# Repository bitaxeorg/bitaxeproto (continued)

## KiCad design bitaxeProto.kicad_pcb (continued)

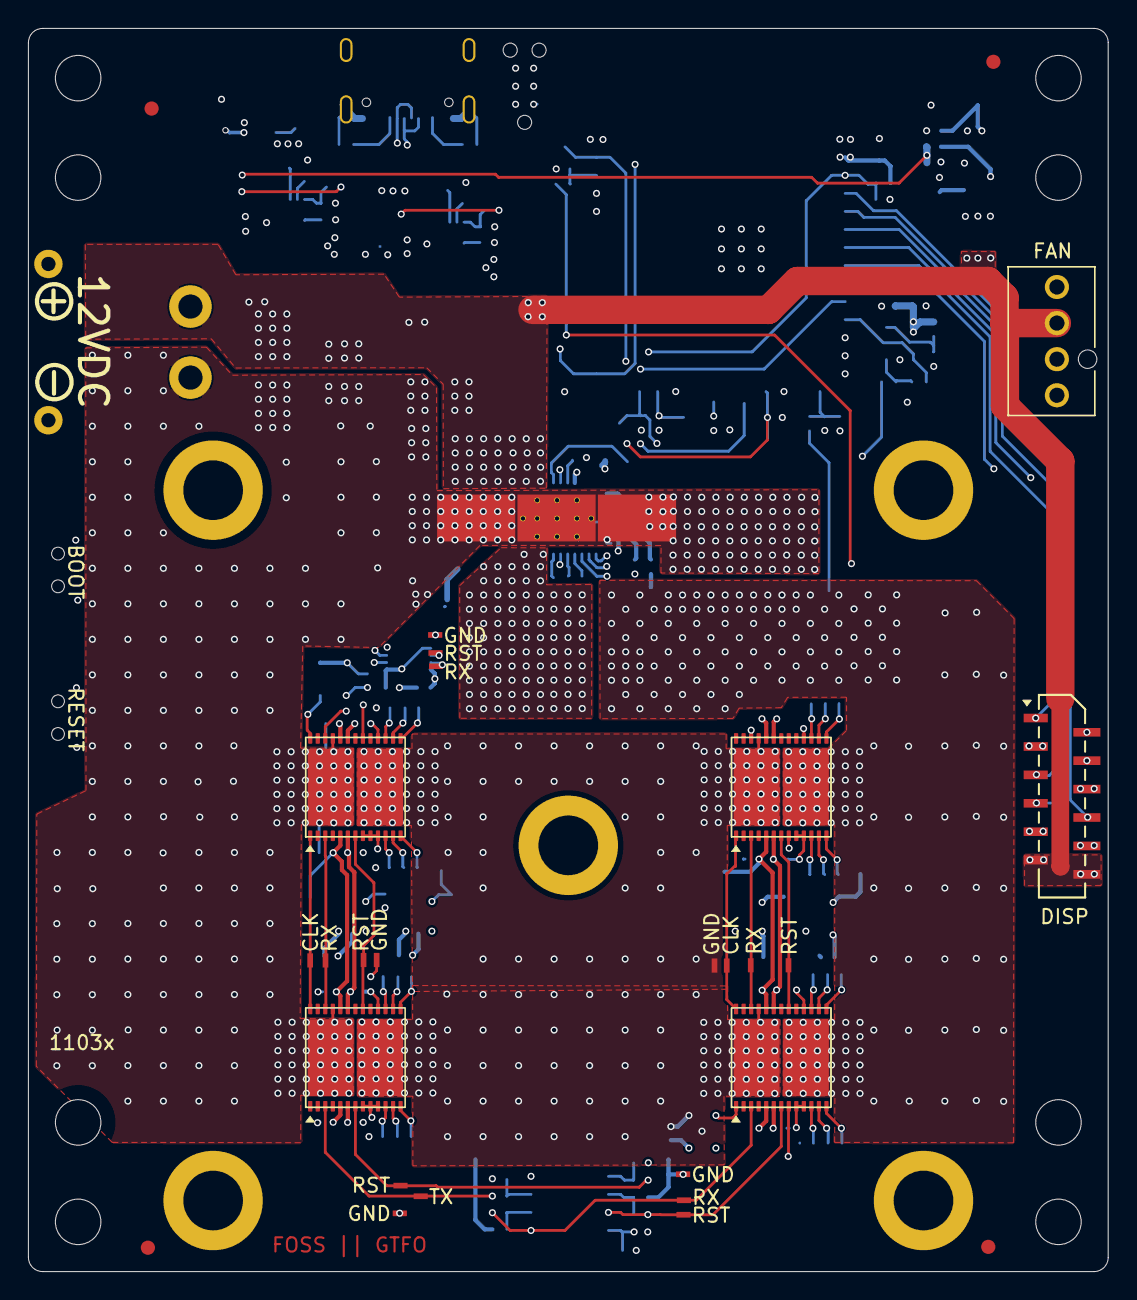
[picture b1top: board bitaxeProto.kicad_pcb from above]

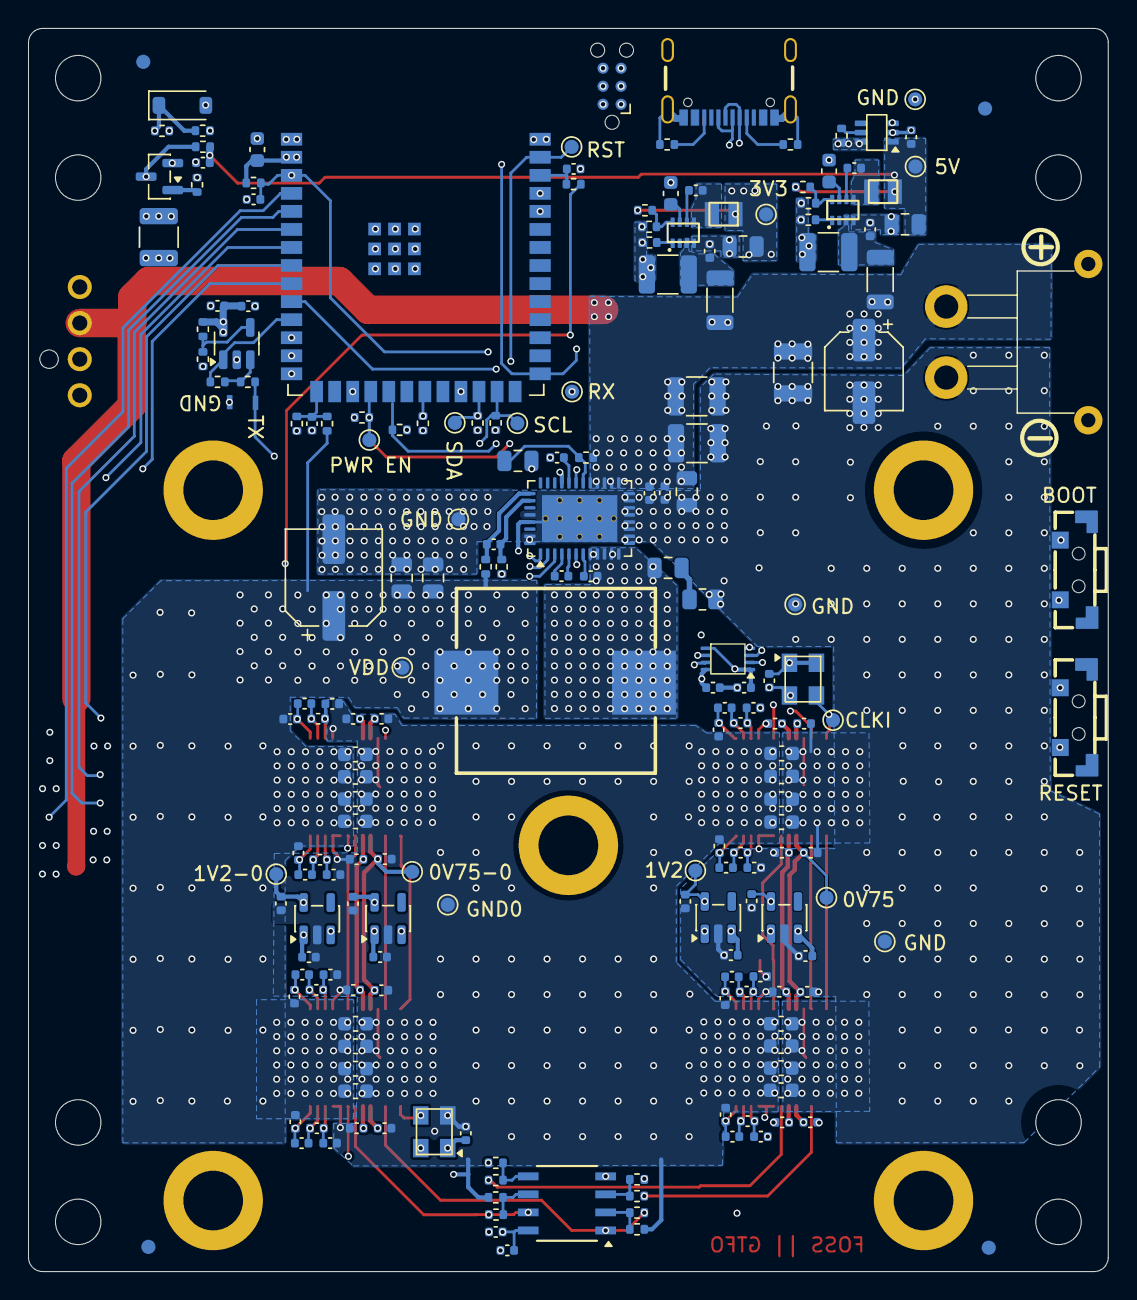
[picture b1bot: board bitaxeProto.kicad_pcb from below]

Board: 6 copper layers, 76.0 x 87.5 mm, 237 parts (204 on the bottom side), 109 nets.

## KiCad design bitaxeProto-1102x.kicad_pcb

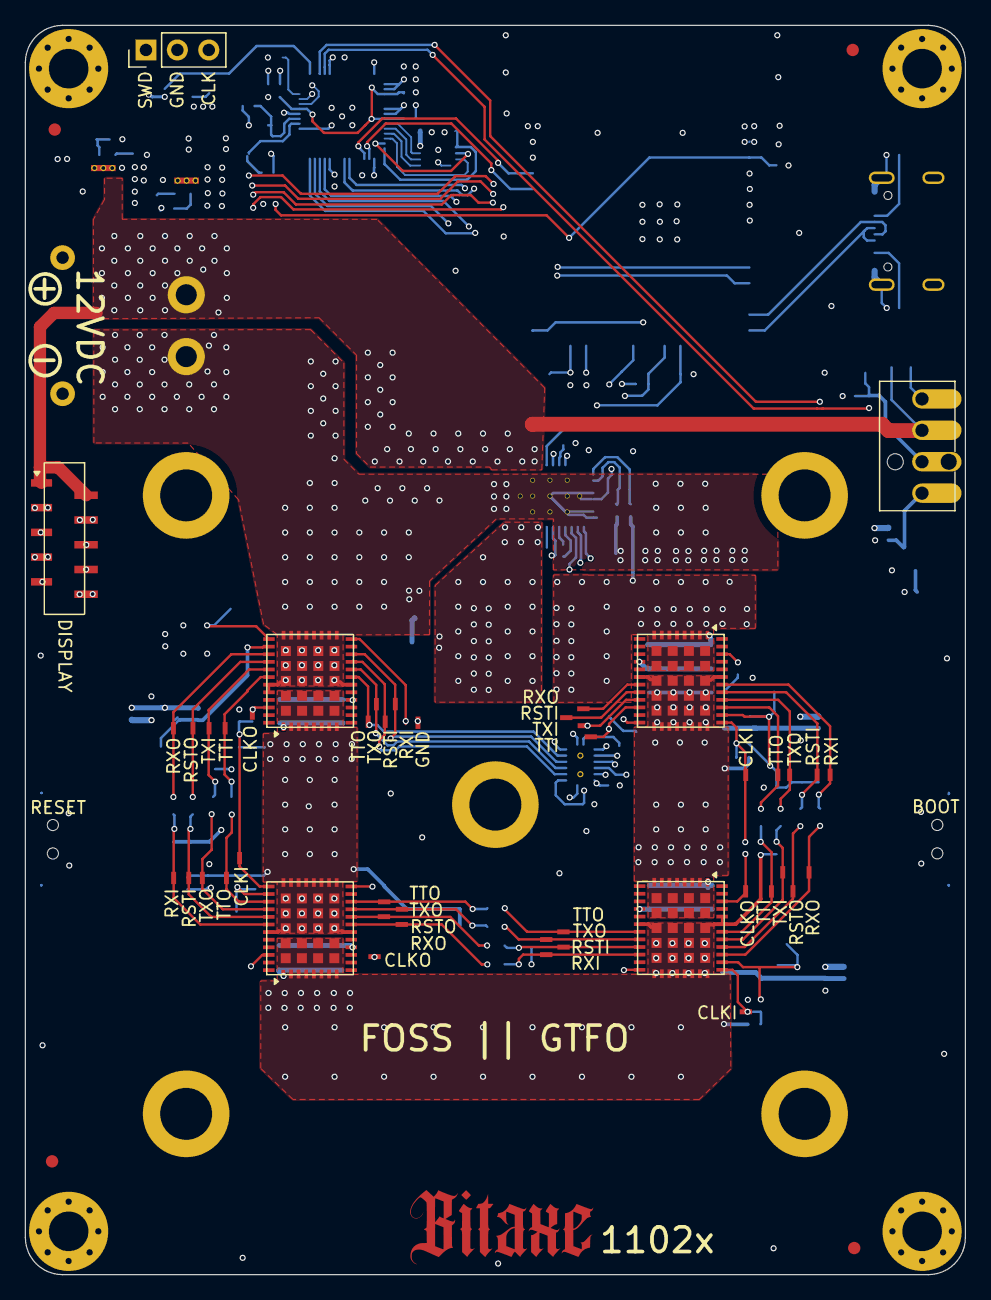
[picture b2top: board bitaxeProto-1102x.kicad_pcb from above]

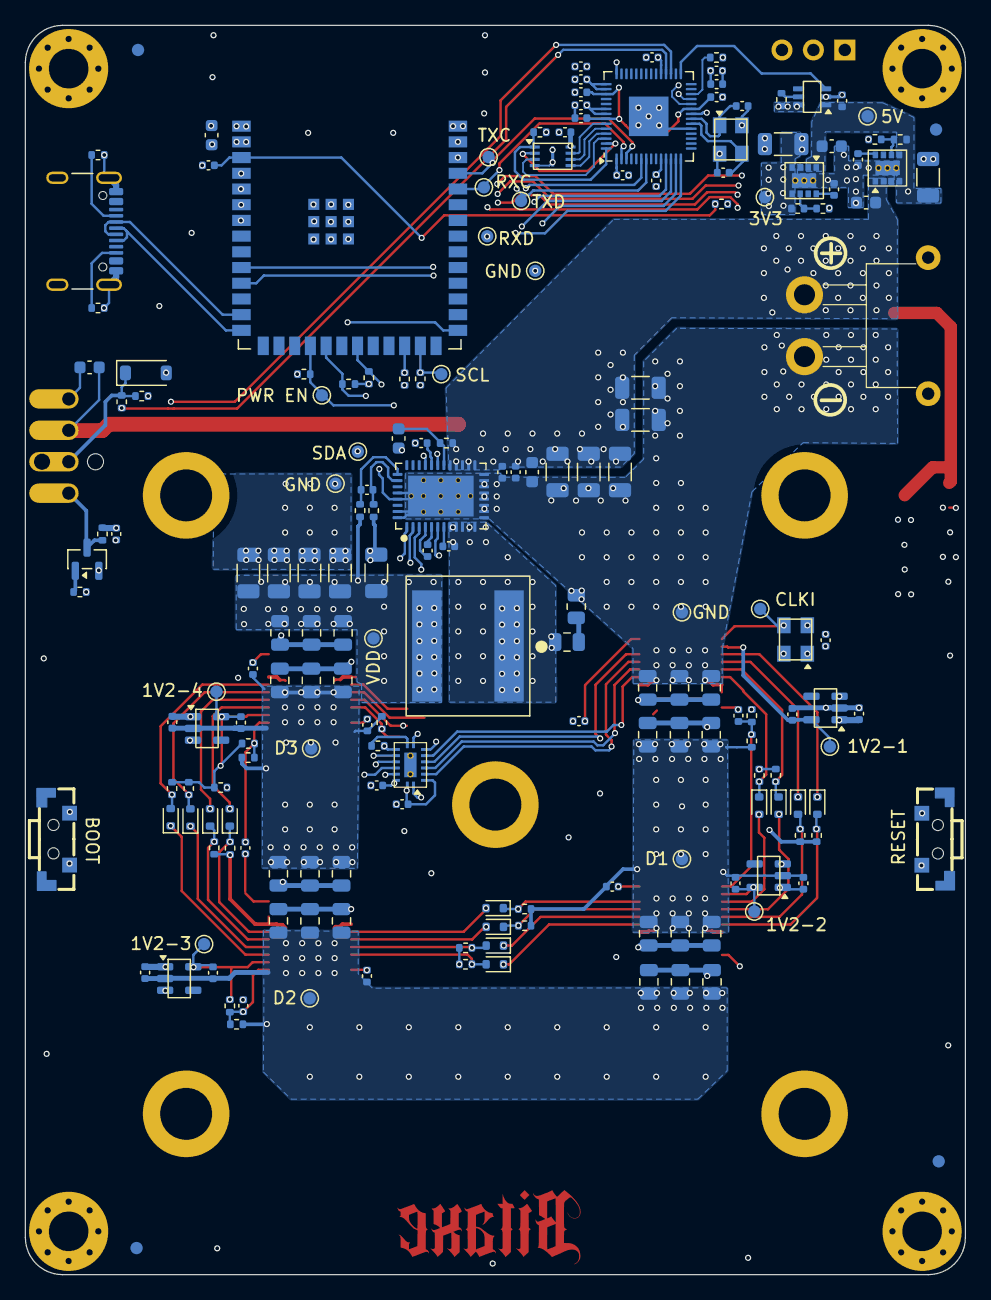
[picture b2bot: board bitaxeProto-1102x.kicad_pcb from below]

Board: 6 copper layers, 76.0 x 101.0 mm, 241 parts (188 on the bottom side), 122 nets.

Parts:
A1, A3: BZM2_MODE0; bzm2
A2, A4: BZM2_MODE1; bzm2
C1, C8, C47, C76: 10uF; C_0603_1608Metric
C2, C3, C4, C5, C6, C30, C31: 22uF; C_1206_3216Metric
C7, C15, C19, C25, C26, C27, C28, C34, C38, C39, C68, C72: 1uF; C_0402_1005Metric
C9, C10: 1uF; C_0603_1608Metric
C11: 4.7uF; C_0402_1005Metric
C12, C29: 3.3nF; C_0402_1005Metric
C13: 4.7nF; C_0402_1005Metric
C14: 2.2nF; C_0402_1005Metric
C16, C32, C36, C37, C40, C41, C42, C43, C44, C45, C46, C57, C58, C59, C77: 0.1uF; C_0402_1005Metric
C17: 1000pF; C_0805_2012Metric
C18: 100pF; C_0402_1005Metric
C20: 47uF; C_1206_3216Metric
C21, C22, C23, C24: 100uF; C_1206_3216Metric
C33, C35: 30pF; C_0402_1005Metric
C48: 12pF; C_0402_1005Metric
C60, C61, C62, C63, C64: 120pF; C_0402_1005Metric
C83, C84, C85, C91, C92, C93, C99, C100, C101, C107, C108, C109, C115, C116, C117, C123, C124, C125, C131, C132, C133, C139, C140, C141: 100uF; C_0805_2012Metric
C142, C143, C144: 1000pF; C_0402_1005Metric
D1, D2, D3, D4, D5, D6, D7, D8, D9, D10, D11, D12: DLLFSD01T-7; D_SOD-523
D13: 3.3V Zener; D_SOD-123
FID1, FID2, FID3, FID4: Fiducial; Fiducial_1mm_Mask2mm
H1, H2, H3, H4: MountingHole_Pad; MountingHole_3.2mm_M3_Pad_Via
HS1: Heatsink; Heatsink-5hole-BitaxeGT
J1: XT30; XT30PW-M
J2: Conn_01x03; PinHeader_1x03_P2.54mm_Vertical
J4: Conn_01x04; 470531000
J5: Conn_01x10; CONN10_1-1735042-0
J6: USB_C_Receptacle_USB2.0; USB_C_Receptacle_GCT_USB4105-xx-A
L1: 1.2uH; XAL1060122MEC
NT1: NetTie_2; NetTie-2_SMD_Pad0.2mmx1mm
Q1: BSS138; SOT-23
R1, R4, R17, R35, R36, R37, R38, R39, R40, R41, R42, R43, R44, R45, R46, R47, R48, R49, R50, R51, R52: 1k; R_0402_1005Metric
R2, R3, R9, R14, R22, R34: 10k; R_0402_1005Metric
R5: 10; R_0402_1005Metric
R6: 1; R_0805_2012Metric
R7, R8: 49.9; R_0402_1005Metric
R10: 536k; R_0402_1005Metric
R11, R13: 100k; R_0402_1005Metric
R12: 309k; R_0402_1005Metric
R16: 49.9k; R_0402_1005Metric
R18, R19, R20, R21: 4.7k; R_0402_1005Metric
R23, R24: 5.1k; R_0402_1005Metric
R26: 20k; R_0402_1005Metric
R33: 5.6k; R_0402_1005Metric
SW3, SW4: SWITCH-SPST; SW-SMD_TC-S3601-3.5-260G-F0.6
TP1: PWR EN; TestPoint_Pad_D1.0mm
TP2: 1V2-2; TestPoint_Pad_D1.0mm
TP3: 1V2-3; TestPoint_Pad_D1.0mm
TP4: 1V2-4; TestPoint_Pad_D1.0mm
TP5: SDA; TestPoint_Pad_D1.0mm
TP6, TP13, TP32, TP51, TP55: RSTI; TestPoint_Pad_1.0x0.4mm
TP7: VDD; TestPoint_Pad_D1.0mm
TP8: SCL; TestPoint_Pad_D1.0mm
TP9: 3V3; TestPoint_Pad_D1.0mm
TP10: CLKI; TestPoint_Pad_D1.0mm
TP11, TP28, TP43: TTI; TestPoint_Pad_1.0x0.4mm
TP12, TP29, TP44: TXI; TestPoint_Pad_1.0x0.4mm
TP14, TP31, TP38, TP46: RXO; TestPoint_Pad_1.0x0.4mm
TP15: 5V; TestPoint_Pad_D1.0mm
TP16: TXC; TestPoint_Pad_D1.0mm
TP17, TP33, TP40, TP50, TP54: TXO; TestPoint_Pad_1.0x0.4mm
TP18: 1V2-1; TestPoint_Pad_D1.0mm
TP19, TP26, TP27: GND; TestPoint_Pad_D1.0mm
TP20, TP36, TP52, TP56: RXI; TestPoint_Pad_1.0x0.4mm
TP21, TP34, TP41, TP49, TP53: TTO; TestPoint_Pad_1.0x0.4mm
TP22: GND; TestPoint_Pad_1.0x0.4mm
TP23: RXC; TestPoint_Pad_D1.0mm
TP24: TXD; TestPoint_Pad_D1.0mm
TP25: RXD; TestPoint_Pad_D1.0mm
TP30, TP39, TP45: RSTO; TestPoint_Pad_1.0x0.4mm
TP35, TP48, TP57: CLKI; TestPoint_Pad_1.0x0.4mm
TP37, TP42, TP47: CLKO; TestPoint_Pad_1.0x0.4mm
TP58: D1; TestPoint_Pad_D1.0mm
TP59: D2; TestPoint_Pad_D1.0mm
TP60: D3; TestPoint_Pad_D1.0mm
U1, U3, U4, U6: MCP1824T-1202E/OT; SOT-23-5
U2: TPS546D24SRVFR; LQFN40-CLIP
U5: W25Q16JVUXIQ TR; USON-8_UX_2x3x0p6_WIN
U7, U10: TPS82130; Texas_SIL0008D_MicroSiP-8-1EP_2.8x3mm_P0.65mm_EP1.1x1.9mm_T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
U8: SN74AXC4T774; BQB0016A-MFG
U9: TPS22919DCKR; DCK0006A_N
U11: RP2040; RP2040-QFN-56-1EP_7x7mm_P0.4mm_EP3.2x3.2mm
U12: ESP32-S3-WROOM-1
Y1: 12MHz; XTAL_ECS-120-20-33-CKM-TR3
Y2: 50MHz; OSC_ECS-3225MV-500-CN-TR

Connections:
/3V3: C31.2, C32.2, C39.2, C40.2, C41.2, C42.2, C43.2, C44.2, C45.2, C46.2, C47.1, C59.1, R12.2, R14.1, R16.2, R18.1, R19.2, R20.2, R21.2, R22.2, R33.2, TP9.1 (1_1), U5.8 (VCC), U8.15 (VCCB), U10.4 (VOUT), U10.5 (VOUT), U11.1 (IOVDD), U11.10 (IOVDD), U11.22 (IOVDD), U11.33 (IOVDD), U11.42 (IOVDD), U11.43 (ADC_AVDD), U11.44 (VREG_IN), U11.48 (USB_VDD), U11.49 (IOVDD), U12.2 (3V3)
/5V: C8.2, C30.2, C34.1, C77.1, R10.2, R34.2, TP15.1 (1_1), U7.4 (VOUT), U7.5 (VOUT), U9.1 (IN), U10.1 (EN), U10.2 (VIN)
/5V_SWITCH: C7.2, C25.2, C27.2, C68.2, R17.1, U1.1 (VIN), U1.3 (EN), U3.1 (VIN), U3.3 (EN), U4.1 (VIN), U4.3 (EN), U6.1 (VIN), U6.3 (EN), U9.6 (OUT)
/12V: C1.2, C2.1, C3.1, C4.1, C5.1, C6.1, C9.1, C13.1, C14.1, C76.1, J1.1 (+V), J4.2, J5.1, J5.2, R5.1, U2.21 (PVIN), U2.22 (PVIN), U2.23 (PVIN), U2.24 (PVIN), U2.25 (PVIN), U7.1 (EN), U7.2 (VIN)
/ASIC/1V2-1: A1.30 (VDDIO), C57.1, C58.1, C72.2, TP18.1 (1_1), U6.5 (VOUT), U8.2 (DIR2), U8.8 (DIR4), U8.16 (VCCA), Y2.1 (EN), Y2.4 (VIN)
/ASIC/1V2-2: A2.30 (VDDIO), C19.2, R37.2, R38.1, R39.1, TP2.1 (1_1), U1.5 (VOUT)
/ASIC/1V2-3: A3.30 (VDDIO), C26.2, R43.2, R44.1, R45.1, TP3.1 (1_1), U3.5 (VOUT)
/ASIC/1V2-4: A4.30 (VDDIO), C28.2, R4.1, R49.2, R50.1, R51.1, TP4.1 (1_1), U4.5 (VOUT)
/ASIC/GND2: A1.2 (VDD), A1.3 (VDD), A1.4 (VDD), A1.5 (VDD), A1.6 (VDD), A1.7 (VDD), A1.8 (VDD), A1.41 (VDD), A1.42 (VDD), A1.49 (VDD), A1.50 (VDD), A1.51 (VDD), A1.52 (VDD), A1.59 (VDD), A1.60 (VDD), A2.14 (VSS), A2.21 (VSS), A2.22 (VSS), A2.23 (VSS), A2.24 (VSS), A2.25 (VSS), A2.26 (VSS), A2.27 (VSS), A2.28 (VSS), A2.35 (VSS), A2.43 (VSS), A2.44 (VSS), A2.45 (VSS), A2.46 (VSS), A2.47 (VSS), A2.48 (VSS), A2.53 (VSS), A2.54 (VSS), A2.55 (VSS), A2.56 (VSS), A2.57 (VSS), A2.58 (VSS), C7.1, C19.1, C63.2, C83.2, C84.2, C85.2, C107.1, C108.1, C109.1, R40.2, R41.2, R42.2, TP58.1 (1_1), U1.2 (GND)
/ASIC/GND3: A2.2 (VDD), A2.3 (VDD), A2.4 (VDD), A2.5 (VDD), A2.6 (VDD), A2.7 (VDD), A2.8 (VDD), A2.41 (VDD), A2.42 (VDD), A2.49 (VDD), A2.50 (VDD), A2.51 (VDD), A2.52 (VDD), A2.59 (VDD), A2.60 (VDD), A3.14 (VSS), A3.21 (VSS), A3.22 (VSS), A3.23 (VSS), A3.24 (VSS), A3.25 (VSS), A3.26 (VSS), A3.27 (VSS), A3.28 (VSS), A3.35 (VSS), A3.36 (PINSEL), A3.43 (VSS), A3.44 (VSS), A3.45 (VSS), A3.46 (VSS), A3.47 (VSS), A3.48 (VSS), A3.53 (VSS), A3.54 (VSS), A3.55 (VSS), A3.56 (VSS), A3.57 (VSS), A3.58 (VSS), C25.1, C26.1, C62.2, C99.2, C100.2, C101.2, C123.1, C124.1, C125.1, R46.2, R47.2, R48.2, TP59.1 (1_1), U3.2 (GND)
/ASIC/GND4: A3.2 (VDD), A3.3 (VDD), A3.4 (VDD), A3.5 (VDD), A3.6 (VDD), A3.7 (VDD), A3.8 (VDD), A3.41 (VDD), A3.42 (VDD), A3.49 (VDD), A3.50 (VDD), A3.51 (VDD), A3.52 (VDD), A3.59 (VDD), A3.60 (VDD), A4.14 (VSS), A4.21 (VSS), A4.22 (VSS), A4.23 (VSS), A4.24 (VSS), A4.25 (VSS), A4.26 (VSS), A4.27 (VSS), A4.28 (VSS), A4.35 (VSS), A4.43 (VSS), A4.44 (VSS), A4.45 (VSS), A4.46 (VSS), A4.47 (VSS), A4.48 (VSS), A4.53 (VSS), A4.54 (VSS), A4.55 (VSS), A4.56 (VSS), A4.57 (VSS), A4.58 (VSS), C27.1, C28.1, C60.2, C61.2, C115.2, C116.2, C117.2, C139.1, C140.1, C141.1, R9.2, R52.2, TP60.1 (1_1), U4.2 (GND)
/ASIC/REFCLKIN1: A1.29 (REFCLKIN), TP10.1 (1_1), Y2.3 (OUT)
/ASIC/REFCLKIN2: A2.29 (REFCLKIN), C142.2, R39.2, R40.1, TP35.1 (1_1)
/ASIC/REFCLKIN3: A3.29 (REFCLKIN), C143.2, R45.2, R46.1, TP57.1 (1_1)
/ASIC/REFCLKIN4: A4.29 (REFCLKIN), C144.2, R51.2, R52.1, TP48.1 (1_1)
/ASIC/REFCLKOUT1: A1.38 (REFCLKOUT1), C142.1, TP37.1 (1_1)
/ASIC/REFCLKOUT2: A2.38 (REFCLKOUT1), C143.1, TP42.1 (1_1)
/ASIC/REFCLKOUT3: A3.38 (REFCLKOUT1), C144.1, TP47.1 (1_1)
/ASIC/RST_1V2: A1.17 (RESET_IN), TP6.1 (1_1), U8.3 (A1)
/ASIC/RST_3V3: U8.14 (B1), U11.14 (GPIO11)
/ASIC/RX_1V2: A1.18 (RX_IN), TP20.1 (1_1), U8.5 (A3)
/ASIC/RX_3V3: U8.12 (B3), U11.11 (GPIO8)
/ASIC/TRIP_1V2: A1.15 (TRIP_OUT), TP21.1 (1_1), U8.6 (A4)
/ASIC/TRIP_3V3: U8.11 (B4), U11.13 (GPIO10)
/ASIC/TX_1V2: A1.16 (TX_OUT), TP17.1 (1_1), U8.4 (A2)
/ASIC/TX_3V3: U8.13 (B2), U11.12 (GPIO9)
/ASIC/bypass1-1/out: A1.1 (VDD_INT_1), C83.1, C84.1, C85.1
/ASIC/bypass1-2/in: A1.12 (VDD_INT_2), C91.2, C92.2, C93.2
/ASIC/bypass2-1/out: A2.1 (VDD_INT_1), C99.1, C100.1, C101.1
/ASIC/bypass2-2/in: A2.12 (VDD_INT_2), C107.2, C108.2, C109.2
/ASIC/bypass3-1/out: A3.1 (VDD_INT_1), C115.1, C116.1, C117.1
/ASIC/bypass3-2/in: A3.12 (VDD_INT_2), C123.2, C124.2, C125.2
/ASIC/bypass4-1/out: A4.1 (VDD_INT_1), C131.1, C132.1, C133.1
/ASIC/bypass4-2/in: A4.12 (VDD_INT_2), C139.2, C140.2, C141.2
/ASIC/shifter1-2/RESET_IN: A2.33 (RESET_IN), D3.A, R37.1, TP32.1 (1_1)
/ASIC/shifter1-2/RESET_OUT: A1.32 (RESET_OUT), D3.K, TP30.1 (1_1)
/ASIC/shifter1-2/RX_IN: A2.34 (RX_IN), D4.A, R38.2, TP36.1 (1_1)
/ASIC/shifter1-2/RX_OUT: A1.31 (RX_OUT), D4.K, TP31.1 (1_1)
/ASIC/shifter1-2/TRIP_IN: A1.34 (TRIP_IN), D1.K, R35.1, TP28.1 (1_1)
/ASIC/shifter1-2/TRIP_OUT: A2.31 (TRIP_OUT), D1.A, TP34.1 (1_1)
/ASIC/shifter1-2/TX_IN: A1.33 (TX_IN), D2.K, R36.1, TP29.1 (1_1)
/ASIC/shifter1-2/TX_OUT: A2.32 (TX_OUT), D2.A, TP33.1 (1_1)
/ASIC/shifter2-3/RESET_IN: A3.17 (RESET_IN), D7.A, R43.1, TP55.1 (1_1)
/ASIC/shifter2-3/RESET_OUT: A2.16 (RESET_OUT), D7.K, TP39.1 (1_1)
/ASIC/shifter2-3/RX_IN: A3.18 (RX_IN), D8.A, R44.2, TP56.1 (1_1)
/ASIC/shifter2-3/RX_OUT: A2.15 (RX_OUT), D8.K, TP38.1 (1_1)
/ASIC/shifter2-3/TRIP_IN: A2.18 (TRIP_IN), D5.K, R41.1, TP41.1 (1_1)
/ASIC/shifter2-3/TRIP_OUT: A3.15 (TRIP_OUT), D5.A, TP53.1 (1_1)
/ASIC/shifter2-3/TX_IN: A2.17 (TX_IN), D6.K, R42.1, TP40.1 (1_1)
/ASIC/shifter2-3/TX_OUT: A3.16 (TX_OUT), D6.A, TP54.1 (1_1)
/ASIC/shifter3-4/RESET_IN: A4.33 (RESET_IN), D11.A, R49.1, TP51.1 (1_1)
/ASIC/shifter3-4/RESET_OUT: A3.32 (RESET_OUT), D11.K, TP45.1 (1_1)
/ASIC/shifter3-4/RX_IN: A4.34 (RX_IN), D12.A, R50.2, TP52.1 (1_1)
/ASIC/shifter3-4/RX_OUT: A3.31 (RX_OUT), D12.K, TP46.1 (1_1)
/ASIC/shifter3-4/TRIP_IN: A3.34 (TRIP_IN), D9.K, R47.1, TP43.1 (1_1)
/ASIC/shifter3-4/TRIP_OUT: A4.31 (TRIP_OUT), D9.A, TP49.1 (1_1)
/ASIC/shifter3-4/TX_IN: A3.33 (TX_IN), D10.K, R48.1, TP44.1 (1_1)
/ASIC/shifter3-4/TX_OUT: A4.32 (TX_OUT), D10.A, TP50.1 (1_1)
/Data/1V1: C36.2, C37.2, C38.2, U11.23 (DVDD), U11.45 (VREG_VOUT), U11.50 (DVDD)
/Data/5V_EN: U9.3 (ON), U11.29 (GPIO18)
/Data/DISP_GPIO1: J5.5, U12.4 (GPIO4/TOUCH4/ADC1_CH3)
/Data/DISP_GPIO2: J5.6, U12.5 (GPIO5/TOUCH5/ADC1_CH4)
/Data/DISP_SCL: J5.8, U12.6 (GPIO6/TOUCH6/ADC1_CH5)
/Data/DISP_SDA: J5.9, U12.7 (GPIO7/TOUCH7/ADC1_CH6)
/Data/EN: C48.1, R22.1, SW3.2, U12.3 (EN)
/Data/ESP32_RX_CTRL: TP23.1 (1_1), U11.2 (GPIO0), U12.36 (U0RXD/GPIO44/CLK_OUT2)
/Data/ESP32_RX_DATA: TP25.1 (1_1), U11.6 (GPIO4), U12.11 (GPIO18/U1RXD/ADC2_CH7/CLK_OUT3)
/Data/ESP32_TX_CTRL: TP16.1 (1_1), U11.3 (GPIO1), U12.37 (U0TXD/GPIO43/CLK_OUT1)
/Data/ESP32_TX_DATA: TP24.1 (1_1), U11.7 (GPIO5), U12.10 (GPIO17/U1TXD/ADC2_CH6)
/Data/FAN_PWM: R1.2, U11.31 (GPIO20)
/Data/FAN_TACH: R2.2, U11.32 (GPIO21)
/Data/IO0: SW4.2, U12.27 (GPIO0/BOOT*)
/Data/PWR_EN: R3.2, TP1.1 (1_1), U2.27 (EN/UVLO), U12.18 (GPIO10/TOUCH10/ADC1_CH9/FSPICS0/FSPIIO4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)
/Data/QSPI_SCLK: U5.6 (CLK), U11.52 (QSPI_SCLK)
/Data/QSPI_SD0: U5.5 (DI(IO0)), U11.53 (QSPI_SD0)
/Data/QSPI_SD1: U5.2 (DO(IO1)), U11.55 (QSPI_SD1)
/Data/QSPI_SD2: U5.3 (/WP(IO2)), U11.54 (QSPI_SD2)
/Data/QSPI_SD3: U5.7 (/HOLDOR/RESET(IO3)), U11.51 (QSPI_SD3)
/Data/QSPI_SS: R14.2, U5.1 (/CS), U11.56 (QSPI_SS)
/Data/SCL: R19.1, TP8.1 (1_1), U2.3 (PMB_CLK), U12.25 (GPIO48/SPICLK_N/SUBSPICLK_N_DIFF)
/Data/SDA: R18.2, TP5.1 (1_1), U2.2 (PMB_DATA), U12.24 (GPIO47/SPICLK_P/SUBSPICLK_P_DIFF)
/Data/SMB_ALRT: R20.1, U2.6 (SMB_ALRT), U12.21 (GPIO13/TOUCH13/ADC2_CH2/FSPIQ/FSPIIO7/S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)
/Data/SWCLK: J2.3, U11.24 (SWCLK), U12.39 (GPIO1/TOUCH1/ADC1_CH0)
/Data/SWD: J2.1, U11.25 (SWD), U12.38 (GPIO2/TOUCH2/ADC1_CH1)
/Data/USB_D+: J6.A6 (D+), J6.B6 (D+), U12.14 (GPIO20/U1CTS/ADC2_CH9/CLK_OUT1/USB_D+)
/Data/USB_D-: J6.A7 (D-), J6.B7 (D-), U12.13 (GPIO19/U1RTS/ADC2_CH8/CLK_OUT2/USB_D-)
/Data/XIN: C35.2, U11.20 (XIN), Y1.3
/Data/XOUT: C33.2, U11.21 (XOUT), Y1.1
/Power/AGND: C10.1, NT1.2, U2.29 (MSEL2), U2.37 (AGND)
/Power/BP1v5: C15.1, U2.4 (BP1V5)
/Power/PGOOD: R21.1, U2.1 (PGD), U12.19 (GPIO11/TOUCH11/ADC2_CH0/FSPID/FSPIIO5/S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)
/Power/SW1: C16.2, C17.1, L1.1, U2.8 (SW), U2.9 (SW), U2.10 (SW), U2.11 (SW), U2.12 (SW)
/Power/V5reg_1: C11.2, U2.28 (VDD5)
/VDD: A4.2 (VDD), A4.3 (VDD), A4.4 (VDD), A4.5 (VDD), A4.6 (VDD), A4.7 (VDD), A4.8 (VDD), A4.41 (VDD), A4.42 (VDD), A4.49 (VDD), A4.50 (VDD), A4.51 (VDD), A4.52 (VDD), A4.59 (VDD), A4.60 (VDD), C20.2, C21.2, C22.2, C23.2, C24.2, C131.2, C132.2, C133.2, L1.2, R7.1, TP7.1 (1_1)
/fan/FAN_PWM_PIN: J4.4, Q1.3 (D), R34.1
/fan/FAN_TACH_PIN: D13.1 (K), J4.3, R2.1, R33.1
GND: A1.14 (VSS), A1.21 (VSS), A1.22 (VSS), A1.23 (VSS), A1.24 (VSS), A1.25 (VSS), A1.26 (VSS), A1.27 (VSS), A1.28 (VSS), A1.35 (VSS), A1.36 (PINSEL), A1.43 (VSS), A1.44 (VSS), A1.45 (VSS), A1.46 (VSS), A1.47 (VSS), A1.48 (VSS), A1.53 (VSS), A1.54 (VSS), A1.55 (VSS), A1.56 (VSS), A1.57 (VSS), A1.58 (VSS), C1.1, C2.2, C3.2, C4.2, C5.2, C6.2, C8.1, C9.2, C11.1, C12.1, C13.2, C14.2, C20.1, C21.1, C22.1, C23.1, C24.1, C29.1, C30.1, C31.1, C32.1, C33.1, C34.2, C35.1, C36.1, C37.1, C38.1, C39.1, C40.1, C41.1, C42.1, C43.1, C44.1, C45.1, C46.1, C47.2, C48.2, C57.2, C58.2, C59.2, C64.2, C68.1, C72.1, C76.2, C77.2, C91.1, C92.1, C93.1, D13.2 (A), H1.1 (1_1), H2.1 (1_1), H3.1 (1_1), H4.1 (1_1), J1.2 (GND), J2.2, J4.1, J5.3, J5.4, J5.7, J5.10, J6.A1 (GND), J6.B1 (GND), J6.S1 (SHIELD), NT1.1, Q1.2 (S), R3.1, R6.2, R8.2, R11.1, R13.1, R23.1, R24.1, R26.1, R35.2, R36.2, SW3.1, SW4.1, TP19.1 (1_1), TP22.1 (1_1), TP26.1 (1_1), TP27.1 (1_1), U2.13 (PGND), U2.14 (PGND), U2.15 (PGND), U2.16 (PGND), U2.17 (PGND), U2.18 (PGND), U2.19 (PGND), U2.20 (PGND), U2.36 (NC), U2.39 (BCX_CLK), U2.40 (BCX_DAT), U2.41 (PAD), U5.4 (GND), U5.9 (EPAD), U6.2 (GND), U7.3 (GND), U7.9 (GND), U8.1 (DIR1), U8.7 (DIR3), U8.10 (GND), U9.2 (GND), U10.3 (GND), U10.9 (GND), U11.19 (TESTEN), U11.57 (GND), U12.1 (GND), U12.40 (GND), U12.41 (GND), Y1.2, Y1.4, Y2.2 (GND)
unnamed: A1.20 (REFCLKOUT2), C64.1
unnamed: A2.20 (REFCLKOUT2), C63.1
unnamed: A3.20 (REFCLKOUT2), C62.1
unnamed: A4.38 (REFCLKOUT1), C60.1
unnamed: A4.20 (REFCLKOUT2), C61.1
unnamed: A4.16 (RESET_OUT), TP13.1 (1_1)
unnamed: A4.15 (RX_OUT), TP14.1 (1_1)
unnamed: A4.18 (TRIP_IN), R9.1, TP11.1 (1_1)
unnamed: A4.17 (TX_IN), R4.2, TP12.1 (1_1)
unnamed: C17.2, R6.1
unnamed: J6.A5 (CC1), R23.2
unnamed: J6.B5 (CC2), R24.2
unnamed: Q1.1 (G), R1.1
unnamed: C10.2, R5.2, U2.26 (AVIN)
unnamed: C16.1, U2.7 (BOOT)
unnamed: C15.2, U2.5 (DRTN)
unnamed: C18.2, R8.1, U2.34 (GOSNS)
unnamed: C18.1, R7.2, U2.33 (VOSNS)
unnamed: R10.1, R11.2, U7.6 (FB)
unnamed: C12.2, U7.8 (SS/TR)
unnamed: R26.2, U8.9 (OE)
unnamed: R17.2, U9.5 (QOD)
unnamed: R12.1, R13.2, U10.6 (FB)
unnamed: C29.2, U10.8 (SS/TR)
unnamed: R16.1, U11.26 (RUN)

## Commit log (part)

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2026-05-12 initial import - moving bitaxeBlock onto bitaxeBonanza platform and renaming bitaxeProto-1102x
2026-05-12 move over to bitaxeBlock ASIC sheet
2026-05-12 switch aux voltage regulators to TPS62933
2026-05-12 remove 1102x from filenames
2026-05-17 add footprints and some 3d cad. rough part placements
2026-05-18 a lot more rough component placement
2026-05-18 power plane tweaking
2026-05-26 routing progress
2026-05-26 remove old bzm2 stuff
2026-05-26 lots of signal routing
2026-05-28 lots of DRC fixes. adding power plane via grid.
2026-05-28 add more data test points. Fix ERC & DRC issues
2026-05-28 update schematic BOM and some part substitutions
2026-05-29 switched to larger LDOs. 0.75V -> 0.8V. Tweaked power planes some more
2026-05-29 update readme and render
2026-05-29 fix display connector orientation
2026-05-29 condense symbol libraries into just bitaxe library
2026-05-29 pcb touchup after gerber review
2026-06-20 update U19 footprint for #1. fix TP silkscreen orientation
2026-06-20 update all versions to 1102xx
